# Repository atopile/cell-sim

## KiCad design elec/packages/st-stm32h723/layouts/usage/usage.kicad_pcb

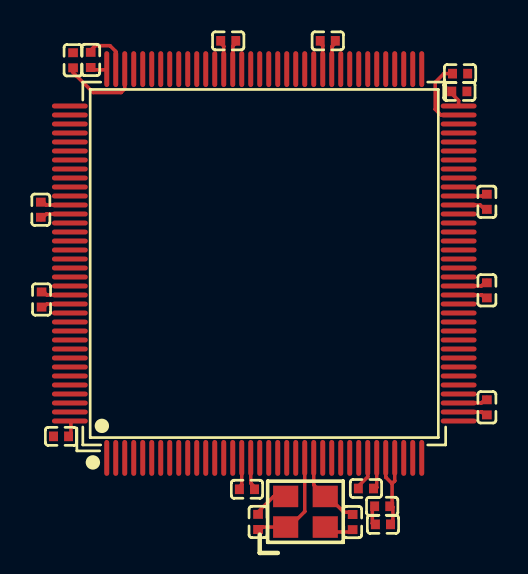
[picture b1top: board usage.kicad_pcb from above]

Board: 2 copper layers, 20 parts (0 on the bottom side), 5 nets.

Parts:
C1, C2, C3, C4, C5, C6, C7, C8, C22, C23, C24, C25, C27: 100nF; C0402
C9, C10: 18pF; C0402
C11, C12: 2.2µF; C0402
C26: 1µF; C0402
U1: LQFP-144_L20.0-W20.0-P0.50-LS22.0-BL
X1: OSC-SMD_4P-L3.2-W2.5-BL_SIT8008BI

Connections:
XIN: C9.1, U1.23, X1.1
XOUT: C10.1, U1.24, X1.3
hv: C1.1, C2.1, C3.1, C4.1, C5.1, C6.1, C7.1, C8.1, C22.1, C23.1, C24.1, C25.1, C26.1, C27.1, U1.17, U1.30, U1.32, U1.33, U1.39, U1.52, U1.62, U1.72, U1.84, U1.95, U1.108, U1.121, U1.131, U1.144
lv: C1.2, C2.2, C3.2, C4.2, C5.2, C6.2, C7.2, C8.2, C9.2, C10.2, C11.2, C12.2, C22.2, C23.2, C24.2, C25.2, C26.2, C27.2, U1.16, U1.31, U1.38, U1.51, U1.61, U1.83, U1.94, U1.107, U1.120, U1.130, X1.2, X1.4
vcap_caps[1]-power-hv: C11.1, C12.1, U1.71, U1.106

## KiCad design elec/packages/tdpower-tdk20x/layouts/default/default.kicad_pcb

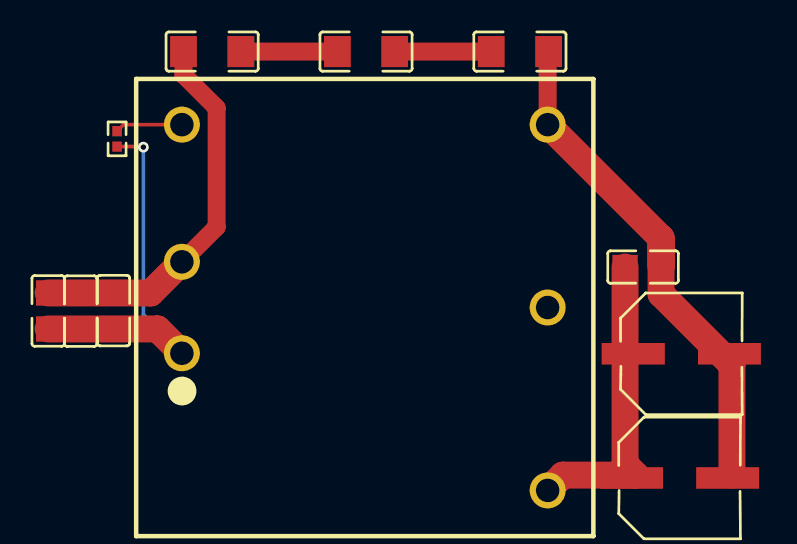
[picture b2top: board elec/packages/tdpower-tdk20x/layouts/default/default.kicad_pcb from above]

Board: 2 copper layers, 11 parts (0 on the bottom side), 7 nets.

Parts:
C1, C2, C3: 10µF; C0805
C4: 1µF; C0805
C5, C6: CAP-SMD_BD6.3-L6.6-W6.6-FD
C7, C8, C9: 2.2nF; C1206
R1: 10kΩ; R0402
U1: PWRM-TH_TDPOWER_TDK20-XXSXXWH

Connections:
CNT: R1.1, U1.3
hv: C1.1, C2.1, C3.1, R1.2, U1.1
lv: C4.2, C5.2, C6.2, C9.2, U1.4
output_cap_1-power-hv: C4.1, C5.1, C6.1, U1.6
y_caps[0]-power-hv: C1.2, C2.2, C3.2, C7.1, U1.2
y_caps[1]-power-hv: C7.2, C8.1
y_caps[2]-power-hv: C8.2, C9.1

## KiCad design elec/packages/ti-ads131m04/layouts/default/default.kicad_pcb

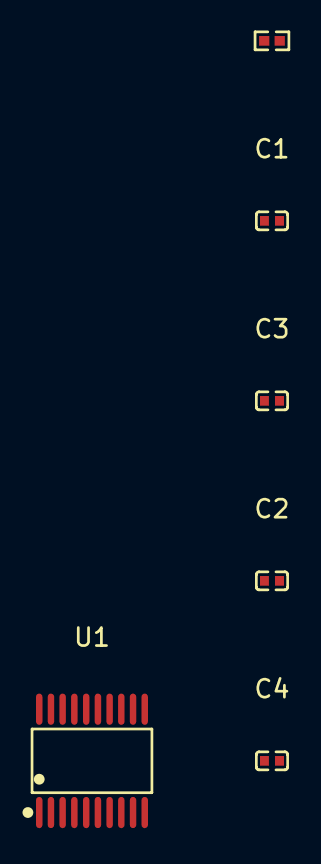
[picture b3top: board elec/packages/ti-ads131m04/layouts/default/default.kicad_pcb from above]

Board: 2 copper layers, 6 parts (0 on the bottom side), 5 nets, no tracks yet.

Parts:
C1, C3: 1µF; C0402
C2, C4: 100nF; C0402
R1: 10kΩ; R0402
U1: TSSOP-20_L6.5-W4.4-P0.65-LS6.4-BL

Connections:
cap_bypass-power-hv: C3.1, U1.18
dvdd_decap-power-hv: C4.1, R1.2, U1.20
hv: C1.1, C2.1, U1.1
lv: C1.2, C2.2, C3.2, C4.2, U1.2, U1.19
nSYNC_nRESET: R1.1, U1.11

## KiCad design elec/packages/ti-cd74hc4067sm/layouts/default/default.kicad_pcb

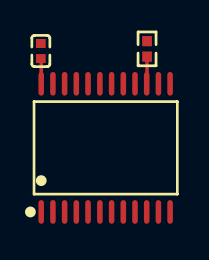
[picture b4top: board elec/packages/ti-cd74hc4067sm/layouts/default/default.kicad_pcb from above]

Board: 2 copper layers, 3 parts (0 on the bottom side), 3 nets.

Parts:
C1: 100nF; C0402
R1: 10kΩ; R0402
U1: SSOP-24_L8.1-W5.3-P0.65-LS7.8-BL

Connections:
hv: C1.1, U1.24
lv: C1.2, R1.1, U1.12
nE: R1.2, U1.15
